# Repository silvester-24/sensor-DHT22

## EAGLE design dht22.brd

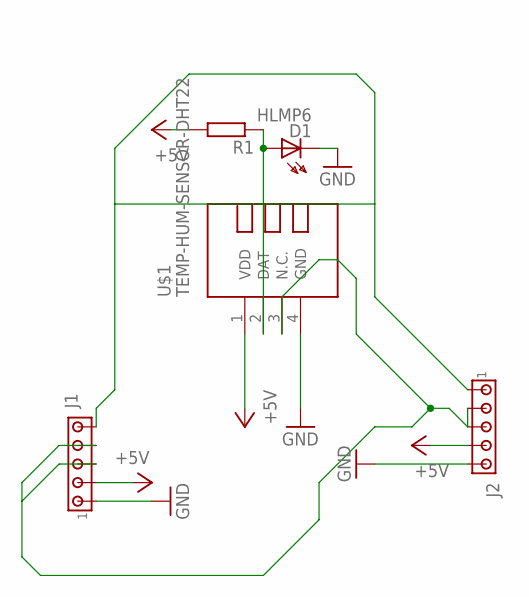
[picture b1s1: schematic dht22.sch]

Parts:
D1: HLMP6
J1, J2: MTA05-100; 10X05MTA
R1: R-EU_0309/10; 0309/10
U$1: TEMP-HUM-SENSOR-DHT22

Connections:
+5V: J1.2, J2.4, R1.2, U$1.1 (VDD)
GND: D1.K, J1.1, J2.5, U$1.4 (GND)
unnamed: D1.A, J1.5, J2.1, R1.1, U$1.2 (DAT)
unnamed: J1.3, J1.4, J2.2, J2.3, U$1.3 (N.C.)

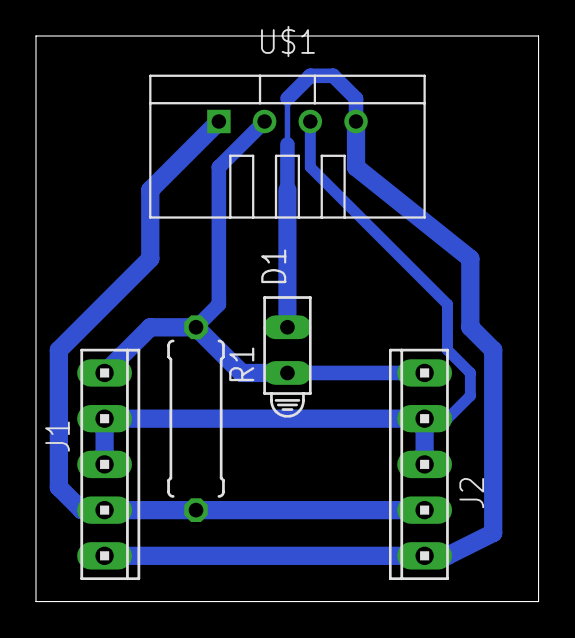
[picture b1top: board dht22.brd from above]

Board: 2 copper layers, 27.9 x 31.4 mm, 5 parts (0 on the bottom side), 4 nets.

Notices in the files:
parts and their libraries:
diy-modules: Released under the Creative Commons Attribution 4.0 International License: http://creativecommons.org/licenses/by/4.0
